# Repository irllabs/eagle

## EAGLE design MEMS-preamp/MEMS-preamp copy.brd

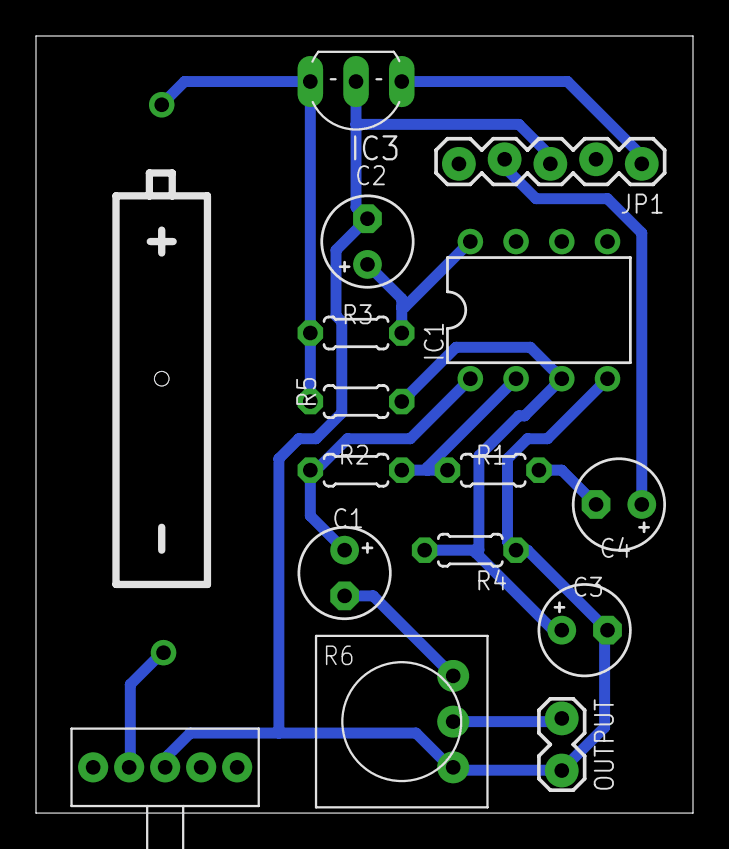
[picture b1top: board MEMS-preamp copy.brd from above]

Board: 2 copper layers, 36.5 x 43.2 mm, 16 parts (0 on the bottom side), 12 nets.

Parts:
BAT1: BATTERY-A23
C1, C4: 10u; E2,5-5
C2: 100u; E2,5-5
C3: 0.1u; E2,5-5
IC1: OPA2134PA; DIL08
IC3: 78; TO92-
JP1: 1X05_LOCK
ON/OFF: labl; SPDT-SWITCH
OUTPUT: 1X02_LOCK
R1: 1K; 0204/5
R2: 100K; 0204/5
R3: 10; 0204/5
R4, R5: 47K; 0204/5
R6: 10K; TRIM-3386

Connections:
+5V: IC3.3, JP1.1
GND: C2.-, C3.-, IC1.4, IC3.2, JP1.3, ON/OFF.2, OUTPUT.2, R4.1, R6.1
unnamed: C2.+, IC1.8, R3.1
unnamed: BAT1.GND@1, ON/OFF.1
unnamed: C4.+, JP1.4
unnamed: C4.-, R1.1
unnamed: IC1.2, R1.2, R2.1
unnamed: C1.-, R6.3
unnamed: OUTPUT.1, R6.2
unnamed: C3.+, IC1.3, R4.2, R5.1
unnamed: C1.+, IC1.1, R2.2
VBAT: BAT1.PWR@1, IC3.1, R3.2, R5.2

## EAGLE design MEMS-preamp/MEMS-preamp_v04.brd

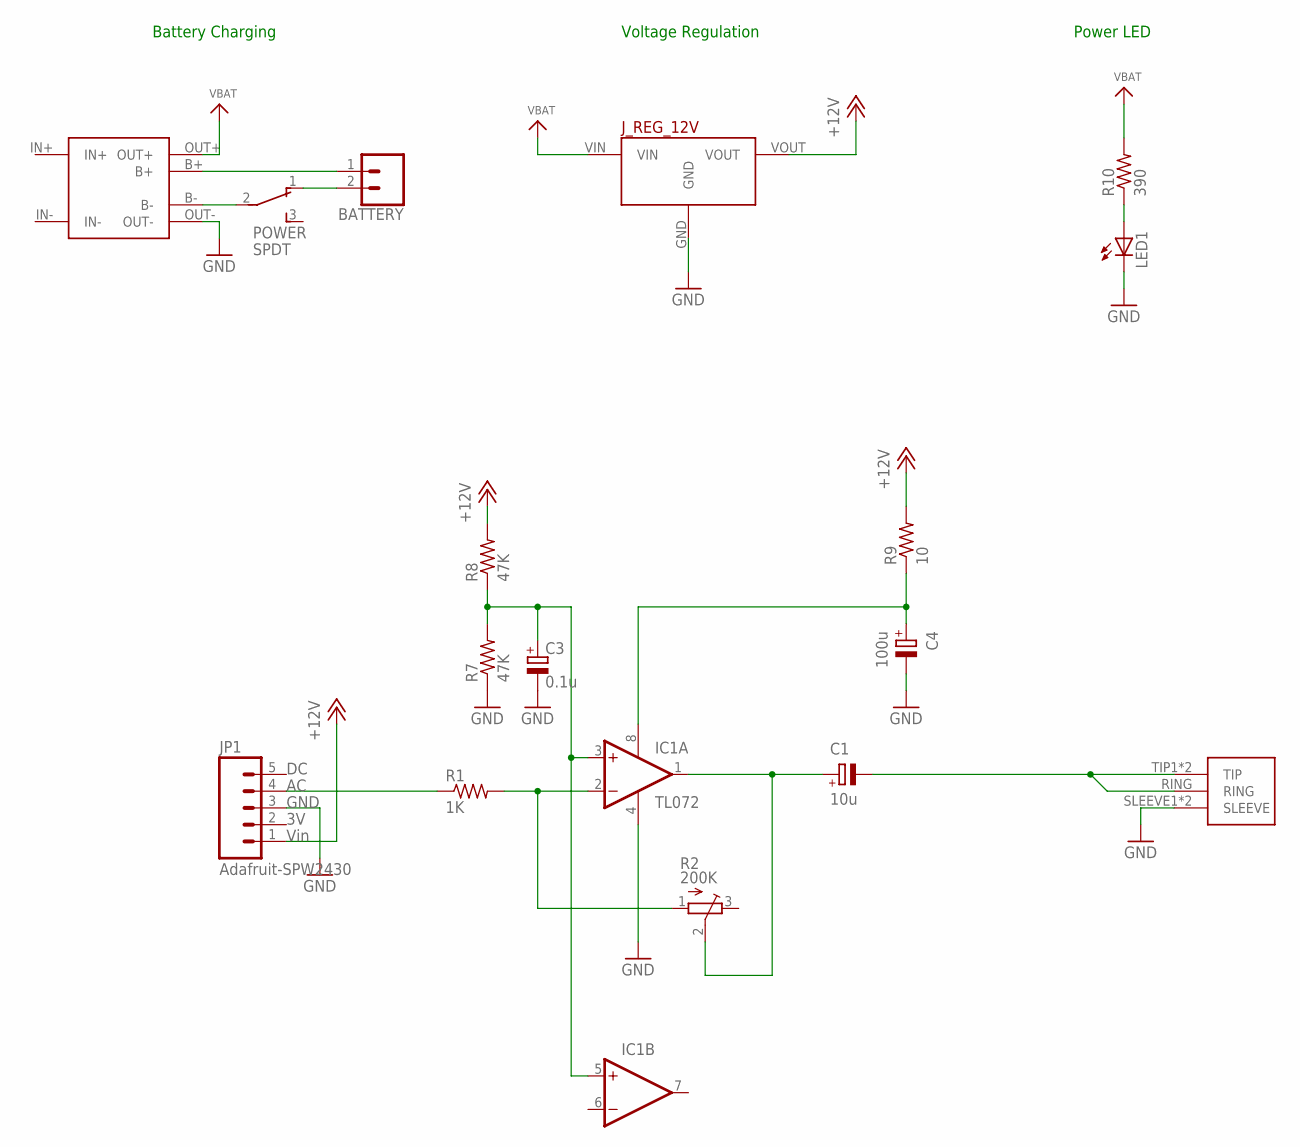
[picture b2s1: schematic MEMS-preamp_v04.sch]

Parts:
BATTERY: CONN_02LOCK; 1X02_LOCK
C1: 10u; E2,5-5
C3: 0.1u; E2,5-5
C4: 100u; E2,5-5
IC1: OPA2134PA; DIL08
JP1: Adafruit-SPW2430; 1X05_LOCK
J_REG_12V: POLOLU_VOLTAGE_REGULATORS_3PIN; POLOLU_5V-12V_STEPUP_U3V12F5-U3V12F12
LED1: LED3MM
POWER: SPDT; SWITCH_SPDT-TE-CONNECT
R1: 1K; 0204/5
R2: 200K; TRIM-3386
R7, R8: 47K; 0204/5
R9: 10; 0204/5
R10: 390; 0204/5
U$1: 1/8"-F-STEREO-PCB
USB-LIPO-CHARGER: TP4056-MODULE; TP4056-LITHIUM-PROTECTED-MODULE

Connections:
+12V: JP1.1, J_REG_12V.VOUT, R8.2, R9.2
GND: C3.-, C4.-, IC1.4 (V-), JP1.3, J_REG_12V.GND, LED1.K (C), R7.1, U$1.SLEEVE1 (SLEEVE), U$1.SLEEVE2 (SLEEVE), USB-LIPO-CHARGER.OUT-
IN+: USB-LIPO-CHARGER.IN+
IN-: USB-LIPO-CHARGER.IN-
unnamed: C4.+, IC1.8 (V+), R9.1
unnamed: BATTERY.2, POWER.1
unnamed: JP1.4, R1.1
unnamed: IC1.2 (-IN), R1.2, R2.1 (A)
unnamed: C1.-, U$1.RING, U$1.TIP1 (TIP), U$1.TIP2 (TIP)
unnamed: C3.+, IC1.3 (+IN), IC1.5 (+IN), R7.2, R8.1
unnamed: C1.+, IC1.1 (OUT), R2.2 (S)
unnamed: LED1.A, R10.1
unnamed: BATTERY.1, USB-LIPO-CHARGER.B+
unnamed: POWER.2, USB-LIPO-CHARGER.B-
VBAT: J_REG_12V.VIN, R10.2, USB-LIPO-CHARGER.OUT+

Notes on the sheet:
Voltage Regulation
Battery Charging
Power LED

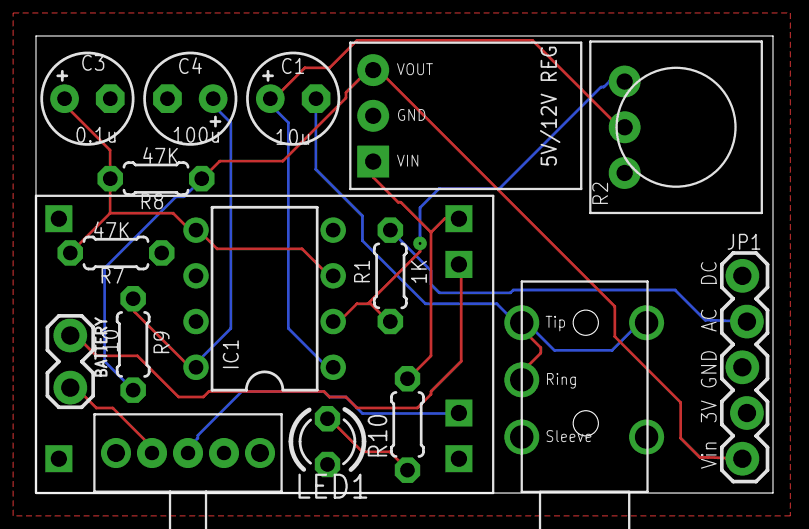
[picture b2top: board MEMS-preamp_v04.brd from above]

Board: 2 copper layers, 40.9 x 25.4 mm, 17 parts (0 on the bottom side), 13 nets.

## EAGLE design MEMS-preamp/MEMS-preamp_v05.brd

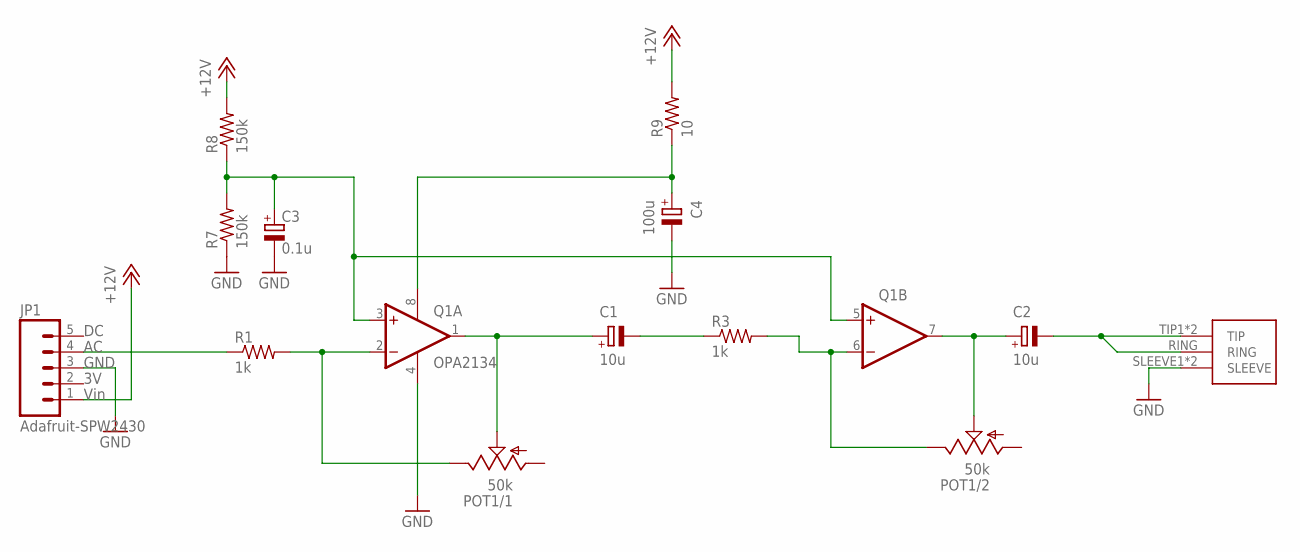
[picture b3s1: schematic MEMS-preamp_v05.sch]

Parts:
C1, C2: 10u; E2,5-5
C3: 0.1u; E2,5-5
C4: 100u; E2,5-5
JP1: Adafruit-SPW2430; 1X05_LOCK
POT1: 50k; PTV112
Q1: OPA2134; DIL08
R1, R3: 1k; 0204/5
R7, R8: 150k; 0204/5
R9: 10; 0204/5
U$1: 1/8"-F-STEREO-PCB

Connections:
+12V: JP1.1, R8.2, R9.2
GND: C3.-, C4.-, JP1.3, Q1.4 (V-), R7.1, U$1.SLEEVE1 (SLEEVE), U$1.SLEEVE2 (SLEEVE)
GROU[: POT1.2.3 (E), Q1.6 (-IN), R3.2
unnamed: C4.+, Q1.8 (V+), R9.1
unnamed: JP1.4, R1.1
unnamed: C1.-, R3.1
unnamed: POT1.1.3 (E), Q1.2 (-IN), R1.2
unnamed: C2.-, U$1.RING, U$1.TIP1 (TIP), U$1.TIP2 (TIP)
unnamed: C3.+, Q1.3 (+IN), Q1.5 (+IN), R7.2, R8.1
unnamed: C1.+, POT1.1.2 (S), Q1.1 (OUT)
unnamed: C2.+, POT1.2.2 (S), Q1.7 (OUT)

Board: 2 copper layers, 13 parts (0 on the bottom side), 11 nets, no tracks yet.

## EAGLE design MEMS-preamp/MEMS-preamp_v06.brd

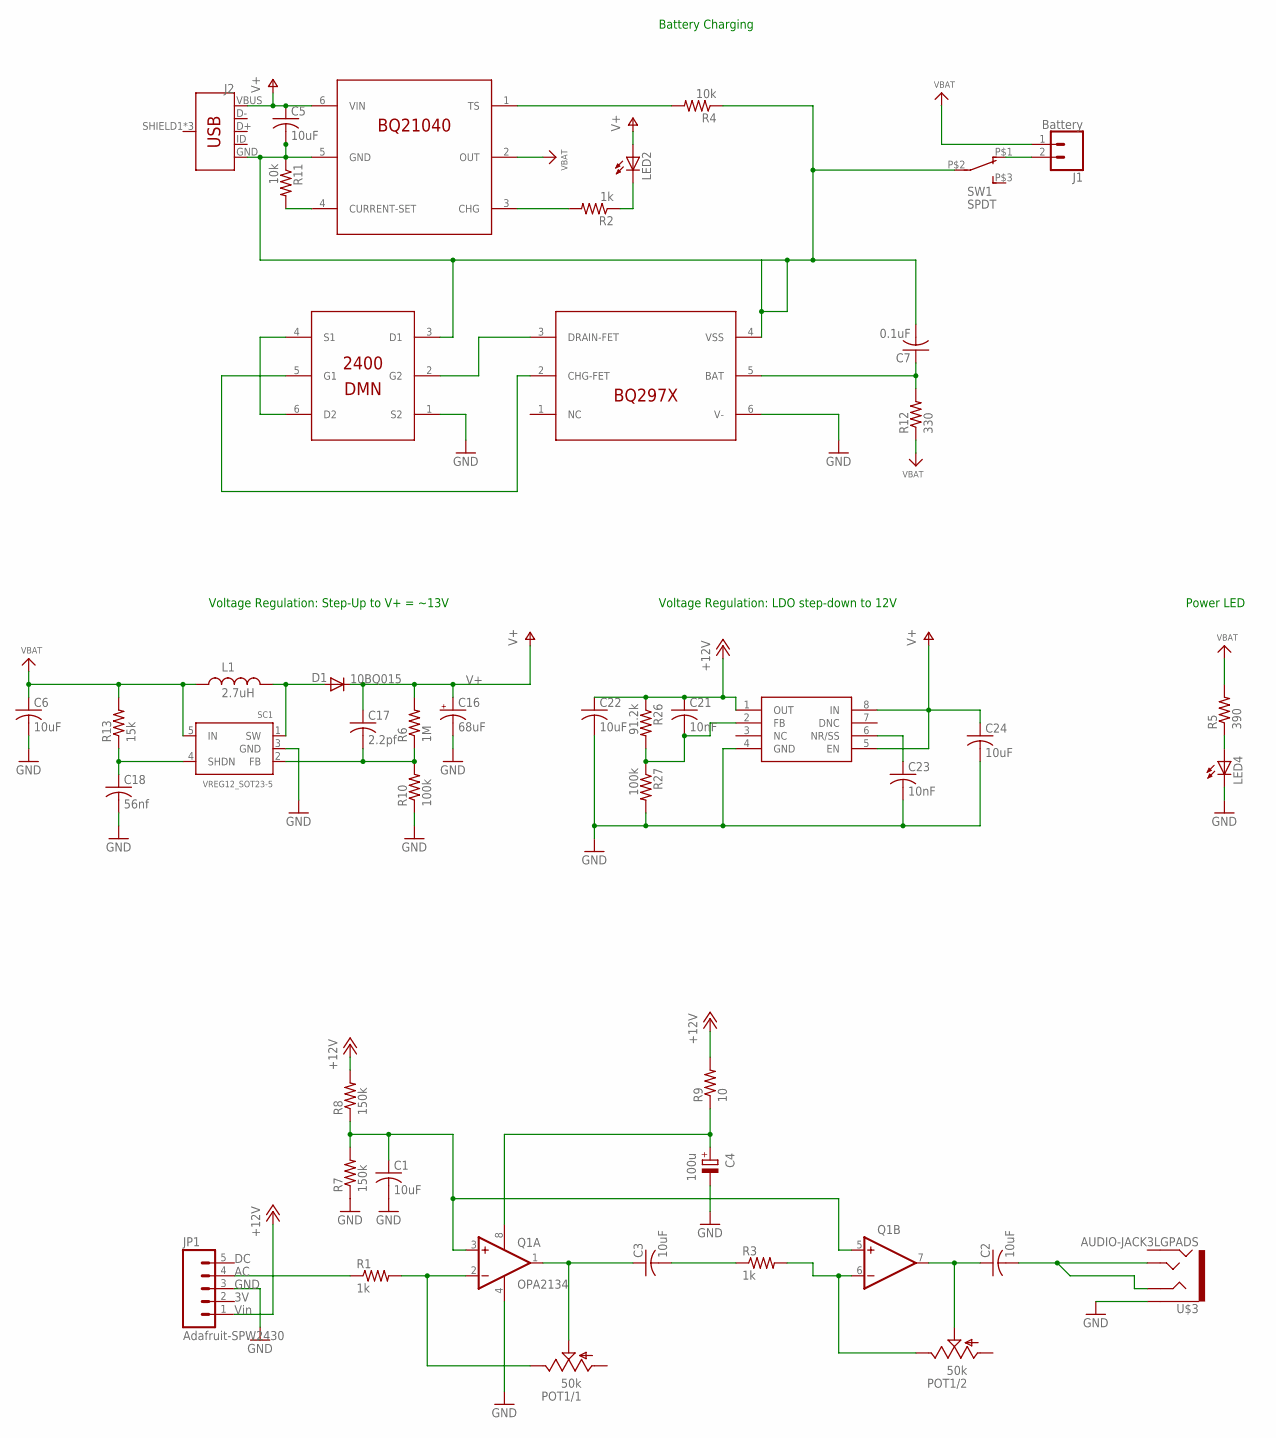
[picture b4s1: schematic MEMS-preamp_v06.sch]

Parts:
C1, C2: 10uF; C0603
C3, C6, C22, C24: 10uF; C0805
C4: 100u; CT7343
C5: 10uF; C0805K
C7: 0.1uF; C0805K
C16: 68uF; EIA3528
C17: 2.2pf; C0805
C18: 56nf; C0805
C21, C23: 10nF; C0805
D1: 10BQ015; SMA-DIODE
J1: Battery; 1X02_LOCK
J2: USB_MICRO-BREDUCED_PASTE; USB-B-MICRO-SMD_RED_PASTE
JP1: Adafruit-SPW2430; 1X05_LOCK
L1: 2.7uH; CR54
LED2, LED4: LED3MM
POT1: 50k; PTV112
Q1: OPA2134; SO08
Q2: BQ21040; SOT23-6
Q5: BQ297X; WSON-6
Q7: DMN2400; SOT-563
R1, R3: 1k; R0603
R2: 1k; R0805
R4, R11: 10k; R0805
R5: 390; R0805
R6: 1M; R0603
R7, R8: 150k; R0603
R9: 10; R0603
R10, R27: 100k; R0603
R12: 330; R0805
R13: 15k; R0603
R26: 91.2k; R0603
SC1: VREG12_SOT23-5; SOT23-5
SW1: SPDT; SWITCH_SPDT_CL-SB-12B
U$3: AUDIO-JACK3LGPADS; TRRS_SJ-43514-SMT-TR
U$13: TPS7A49; MSOP-8

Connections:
+12V: C21.1, C22.1, JP1.1, R8.2, R9.2, R26.1, U$13.1 (OUT)
GND: C1.2, C4.-, C6.2, C16.C (-), C18.2, C22.2, C23.2, C24.2, JP1.3, LED4.K (C), Q1.4 (V-), Q5.6 (V-), Q7.1 (S2), R7.1, R10.1, R27.2, SC1.3 (GND), U$3.EARTH, U$13.4 (GND)
GND2: C5.2, C7.2, J2.GND, Q2.5 (GND), Q5.4 (VSS), Q7.3 (D1), R4.1, R11.1, SW1.P$2 (2)
GROU[: POT1.2.3 (E), Q1.6 (-IN), R3.2
unnamed: C4.+, Q1.8 (V+), R9.1
unnamed: LED4.A, R5.1
unnamed: JP1.4, R1.1
unnamed: C3.2, R3.1
unnamed: POT1.1.3 (E), Q1.2 (-IN), R1.2
unnamed: J1.2, SW1.P$1 (1)
unnamed: C2.2, U$3.RING1, U$3.TIP
unnamed: C1.1, Q1.3 (+IN), Q1.5 (+IN), R7.2, R8.1
unnamed: C3.1, POT1.1.2 (S), Q1.1 (OUT)
unnamed: C2.1, POT1.2.2 (S), Q1.7 (OUT)
unnamed: LED2.K (C), R2.1
unnamed: D1.A, L1.P$2 (2), SC1.1 (SW)
unnamed: C18.1, R13.1, SC1.4 (SHDN)
unnamed: C17.2, R6.1, R10.2, SC1.2 (FB)
unnamed: Q2.3 (CHG), R2.2
unnamed: Q2.1 (TS), R4.2
unnamed: Q2.4 (CURRENT-SET), R11.2
unnamed: C7.1, Q5.5 (BAT), R12.2
unnamed: Q7.4 (S1), Q7.6 (D2)
unnamed: Q5.2 (CHG-FET), Q7.5 (G1)
unnamed: Q5.3 (DRAIN-FET), Q7.2 (G2)
unnamed: C21.2, R26.2, R27.1, U$13.2 (FB)
unnamed: C23.1, U$13.6 (NR/SS)
V+: C5.1, C16.A (+), C17.1, C24.1, D1.C, J2.VBUS, LED2.A, Q2.6 (VIN), R6.2, U$13.5 (EN), U$13.8 (IN)
VBAT: C6.1, J1.1, L1.P$1 (1), Q2.2 (OUT), R5.2, R12.1, R13.2, SC1.5 (IN)

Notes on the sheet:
Voltage Regulation: Step-Up to V+ = ~13V
Power LED
Voltage Regulation: LDO step-down to 12V
Battery Charging

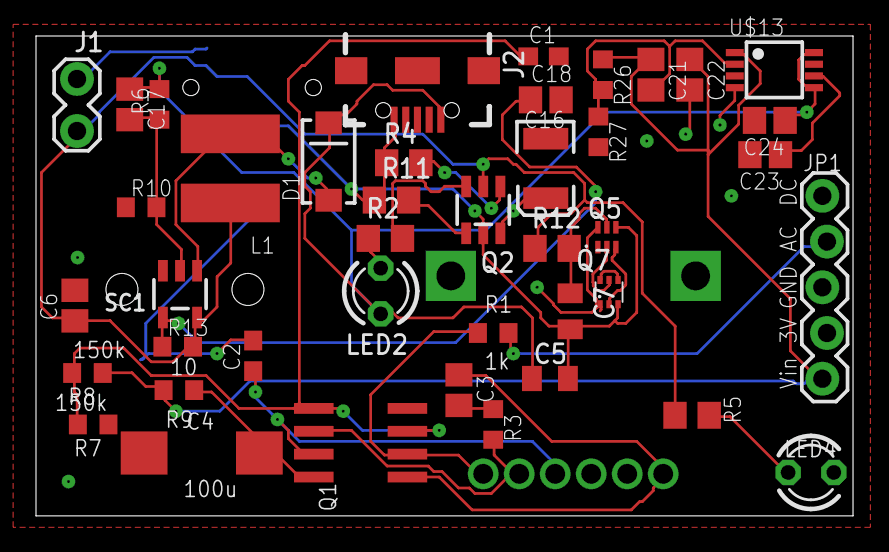
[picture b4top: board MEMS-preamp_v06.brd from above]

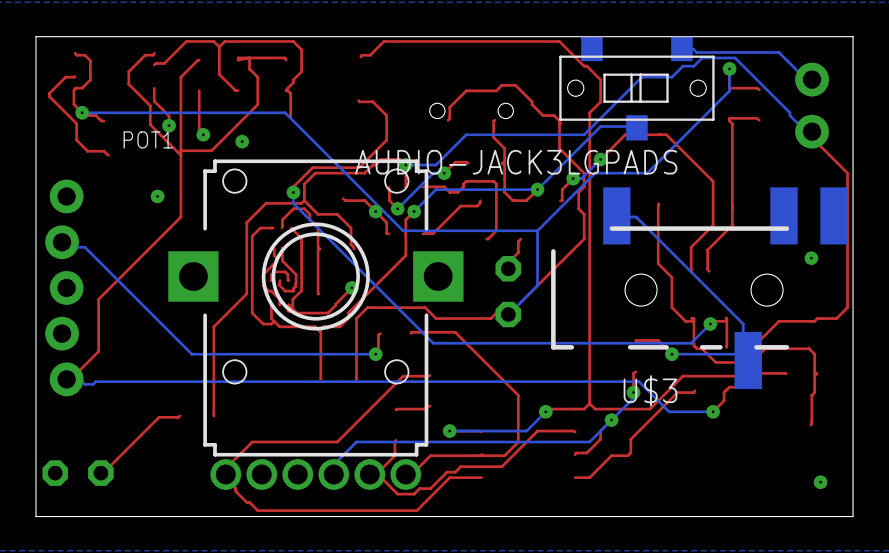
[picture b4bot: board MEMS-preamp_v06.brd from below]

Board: 2 copper layers, 45.4 x 26.7 mm, 45 parts (3 on the bottom side), 29 nets.

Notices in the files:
parts and their libraries:
SparkFun-Connectors: Licensing: Creative Commons ShareAlike 4.0 International - https://creativecommons.org/licenses/by-sa/4.0
microbuilder: This work is placed in the public domain, and may be freely used for commercial and non-commercial work with the following conditions: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
